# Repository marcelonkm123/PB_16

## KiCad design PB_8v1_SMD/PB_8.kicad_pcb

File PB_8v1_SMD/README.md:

# Copyright and Disclaimer
Copyright: Scott Hanson

This documentation describes Open Hardware and is licensed under the CERN Open Hardware Licence Version 2 - Strongly Reciprocal. (CERN-OHL-S)

You may redistribute and modify this documentation under the terms of the CERN OHL-S-v2 (https://ohwr.org/cern_ohl_s_v2.txt). This documentation is distributed WITHOUT ANY EXPRESS OR IMPLIED WARRANTY, INCLUDING OF MERCHANTABILITY, SATISFACTORY QUALITY AND FITNESS FOR A PARTICULAR PURPOSE. Please see the CERN OHL v2-S for applicable conditions

**Under CERN OHL-S-v2, derivative work must be publicy released as defined in subsection 3.3**

# PB 8v1

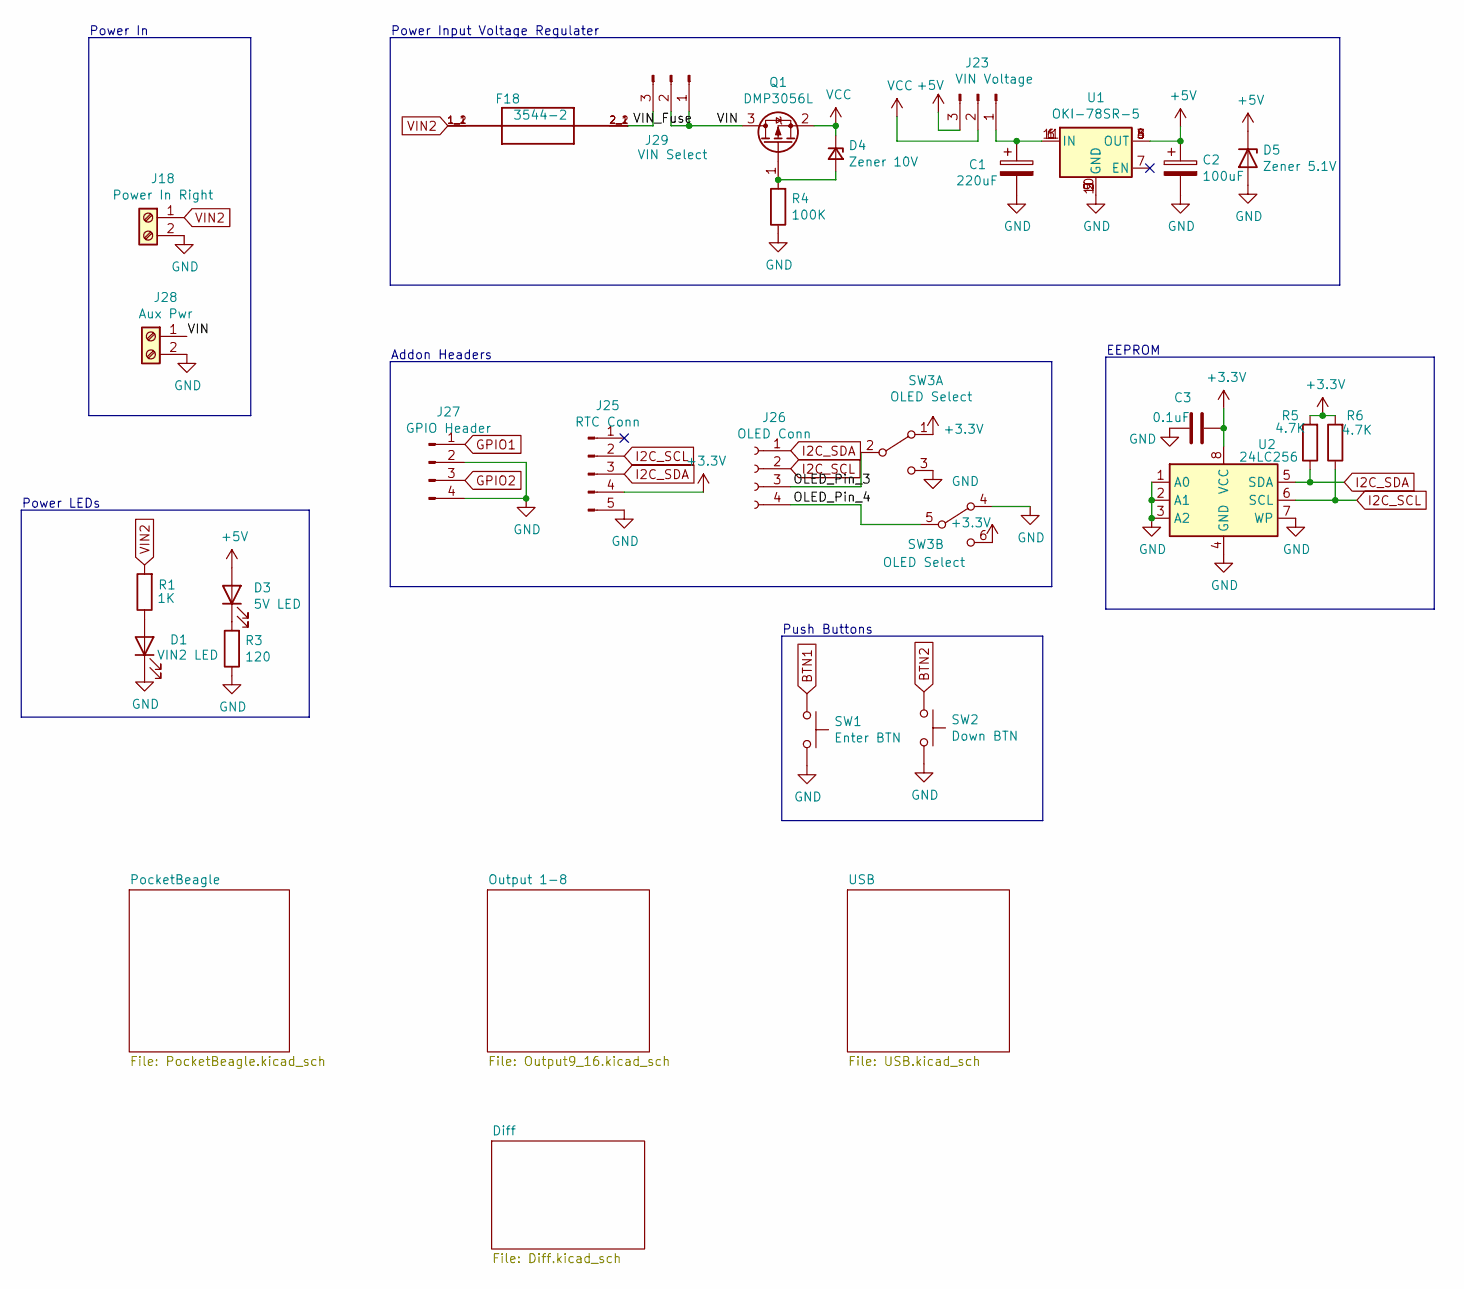
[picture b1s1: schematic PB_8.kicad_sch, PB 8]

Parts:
C1: 220uF; CP_Radial_D10.0mm_P5.00mm; MPN ECA-1HM221; Digi-Key_PN P5183-ND
C2: 100uF; CP_Elec_6.3x5.4_Nichicon; MPN UWX1C101MCL1GB; Digi-Key_PN 493-2105-1-ND
C3: 0.1uF; C_0603_1608Metric_Pad1.08x0.95mm_HandSolder; MPN CL10B104KB8NNWC; Digi-Key_PN 1276-1935-2-ND
D1: VIN2 LED; LED_0603_1608Metric_Pad1.05x0.95mm_HandSolder; MPN LTST-C190KRKT; Digi-Key_PN 160-1436-2-ND
D3: 5V LED; LED_0603_1608Metric_Pad1.05x0.95mm_HandSolder; MPN LTST-C190KRKT; Digi-Key_PN 160-1436-2-ND
D4: Zener 10V; D_SOD-123; MPN MMSZ5240B-7-F; Digi-Key_PN MMSZ5240B-FDICT-ND
D5: Zener 5.1V; D_SOD-123; MPN MMSZ5231B-7-F; Digi-Key_PN MMSZ5231B-FDICT-ND
F18: 3544-2; FUSE_3544-2; MPN 3544-2; Digi-Key_PN 36-3544-2-ND
J18: Power In Right; BARRIER_BLOCK_1ROW_2POS_P9.5MM; MPN OSTYK51102030; Digi-Key_PN ED2953-ND
J23: VIN Voltage; PinHeader_1x03_P2.54mm_Vertical; MPN 61300311121; Digi-Key_PN 732-5316-ND
J25: RTC Conn; PinHeader_1x05_P2.54mm_Vertical; MPN 61300511121; Digi-Key_PN 732-5318-ND
J26: OLED Conn; PinSocket_1x04_P2.54mm_Vertical; MPN PPTC041LFBN-RC; Digi-Key_PN S7002-ND
J27: GPIO Header; JST_XH_B4B-XH-A_1x04_P2.50mm_Vertical; MPN B4B-XH-A(LF)(SN); Digi-Key_PN 455-2249-ND
J28: Aux Pwr; PHOENIX_MKDS1_2-3.81; MPN 1727010; Digi-Key_PN 277-1947-ND
J29: VIN Select; PinHeader_1x03_P2.54mm_Vertical; MPN 61300311121; Digi-Key_PN 732-5316-ND
Q1: DMP3056L; SOT-23; MPN DMP3056L-7; Digi-Key_PN DMP3056L-7DICT-ND
R1: 1K; R_0603_1608Metric_Pad0.98x0.95mm_HandSolder; MPN RC0603FR-071KL; Digi-Key_PN 311-1.00KHRTR-ND
R3: 120; R_0603_1608Metric_Pad0.98x0.95mm_HandSolder; MPN CRGCQ0603F120R; Digi-Key_PN A129677CT-ND
R4: 100K; R_0603_1608Metric_Pad0.98x0.95mm_HandSolder; MPN RT0603BRD07100KL; Digi-Key_PN YAG1235CT-ND
R5, R6: 4.7K; R_0603_1608Metric_Pad0.98x0.95mm_HandSolder; MPN RC0603JR-074K7L; Digi-Key_PN 311-4.7KGRCT-ND
SW1: Enter BTN; SW_Push_1P1T_NO_6x6mm_H9.5mm; MPN PTS645SL50SMTR92 LFS; Digi-Key_PN CKN9088CT-ND
SW2: Down BTN; SW_Push_1P1T_NO_6x6mm_H9.5mm; MPN PTS645SL50SMTR92 LFS; Digi-Key_PN CKN9088CT-ND
SW3: OLED Select; SW_CuK_JS202011CQN_DPDT_Straight; MPN K3-2235D-F1; LCSC C189615
U1: OKI-78SR-5; Universal_5V_Horizontal; MPN OKI-78SR-5/1.5-W36-C; Digi-Key_PN 811-2196-5-ND
U2: 24LC256; SOIC-8_3.9x4.9mm_P1.27mm; MPN 24LC256T-I/SN; Digi-Key_PN 24LC256T-I/SNCT-ND

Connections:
+5V: C2.1, D3.2 (A), D5.1 (K), J23.3, U1.3 (OUT), U1.4 (OUT), U1.8 (OUT); also elsewhere on the board
/OLED_Pin_3: J26.3, SW3.2 (B)
/OLED_Pin_4: J26.4, SW3.5 (B)
/VIN: J28.1, J29.1, J29.2, Q1.3 (D)
/VIN_Fuse: F18.2_1 (2), F18.2_2 (2), J29.3
BTN1: SW1.1; also elsewhere on the board
BTN2: SW2.1; also elsewhere on the board
GPIO1: J27.1; also elsewhere on the board
GPIO2: J27.3; also elsewhere on the board
I2C_SDA: J25.3, J26.1, R5.1, U2.5 (SDA); also elsewhere on the board
unnamed: C1.1, J23.1, U1.1 (IN), U1.6 (IN), U1.11 (IN)
unnamed: D1.2 (A), R1.1
unnamed: D3.1 (K), R3.2
unnamed: D4.2 (A), Q1.1 (G), R4.2
VCC: D4.1 (K), J23.2, Q1.2 (S)
VIN2: F18.1_1 (1), F18.1_2 (1), J18.1, R1.2; also elsewhere on the board

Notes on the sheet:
Power Input Voltage Regulater
Push Buttons
Power LEDs
EEPROM
Power In
Addon Headers

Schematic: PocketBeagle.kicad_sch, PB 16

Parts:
C7: 0.1uF; C_0805_2012Metric_Pad1.15x1.40mm_HandSolder; MPN CL21F104ZBCNNNC; Digi-Key_PN 1276-1007-1-ND
U1: POCKETBEAGLE-SC-569; BEAGLE_POCKETBEAGLE-SC-569; MPN POCKETBEAGLE-SC-569; Digi-Key_PN POCKETBEAGLE-SC-569-ND

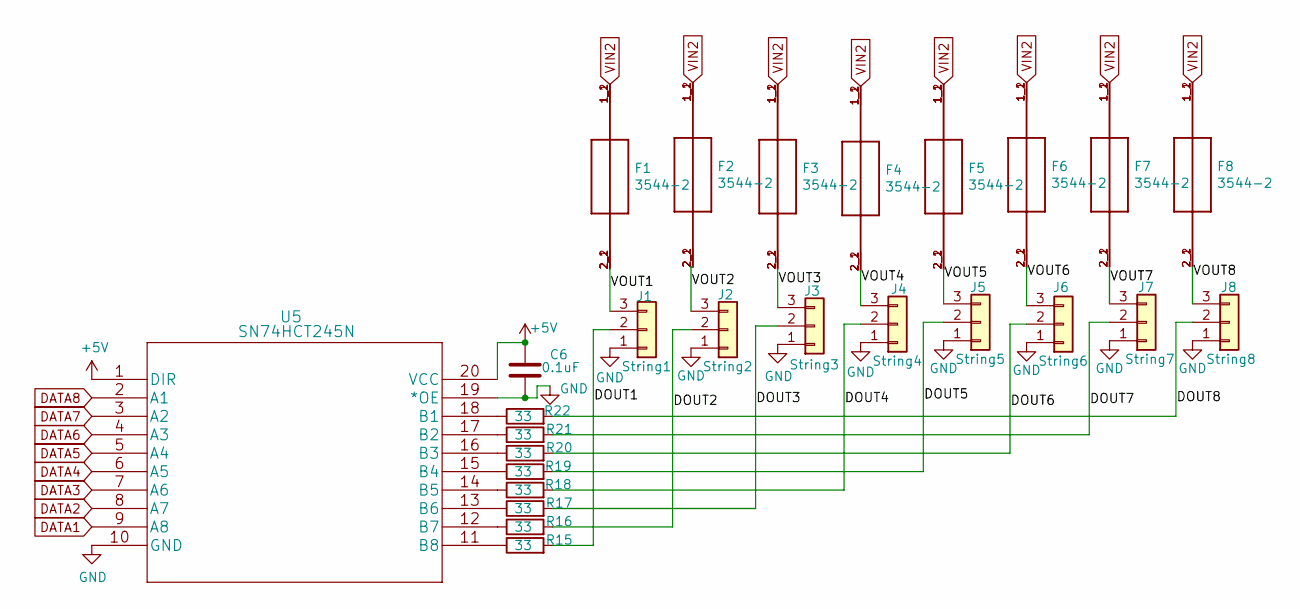
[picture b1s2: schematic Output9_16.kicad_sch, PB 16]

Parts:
C6: 0.1uF; C_0603_1608Metric_Pad1.08x0.95mm_HandSolder; MPN CL10B104KB8NNWC; Digi-Key_PN 1276-1935-2-ND
F1, F2, F3, F4, F5, F6, F7, F8: 3544-2; FUSE_3544-2; MPN 3544-2; Digi-Key_PN 36-3544-2-ND
J1: String1; PhoenixContact_MCV_1,5_3-G-3.5_1x03_P3.50mm_Vertical; MPN 1843619/OSTTJ0311530; Digi-Key_PN 277-5737-ND/ED10555-ND
J2: String2; PhoenixContact_MCV_1,5_3-G-3.5_1x03_P3.50mm_Vertical; MPN 1843619/OSTTJ0311530; Digi-Key_PN 277-5737-ND/ED10555-ND
J3: String3; PhoenixContact_MCV_1,5_3-G-3.5_1x03_P3.50mm_Vertical; MPN 1843619/OSTTJ0311530; Digi-Key_PN 277-5737-ND/ED10555-ND
J4: String4; PhoenixContact_MCV_1,5_3-G-3.5_1x03_P3.50mm_Vertical; MPN 1843619/OSTTJ0311530; Digi-Key_PN 277-5737-ND/ED10555-ND
J5: String5; PhoenixContact_MCV_1,5_3-G-3.5_1x03_P3.50mm_Vertical; MPN 1843619/OSTTJ0311530; Digi-Key_PN 277-5737-ND/ED10555-ND
J6: String6; PhoenixContact_MCV_1,5_3-G-3.5_1x03_P3.50mm_Vertical; MPN 1843619/OSTTJ0311530; Digi-Key_PN 277-5737-ND/ED10555-ND
J7: String7; PhoenixContact_MCV_1,5_3-G-3.5_1x03_P3.50mm_Vertical; MPN 1843619/OSTTJ0311530; Digi-Key_PN 277-5737-ND/ED10555-ND
J8: String8; PhoenixContact_MCV_1,5_3-G-3.5_1x03_P3.50mm_Vertical; MPN 1843619/OSTTJ0311530; Digi-Key_PN 277-5737-ND/ED10555-ND
R15, R16, R17, R18, R19, R20, R21, R22: 33; R_0603_1608Metric_Pad0.98x0.95mm_HandSolder; MPN RC0603FR-0733RL; Digi-Key_PN 311-33.0HRCT-ND
U5: SN74HCT245N; SN74HCT245NSR; MPN SN74HCT245NSR; Digi-Key_PN 296-15849-1-ND

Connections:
+5V: C6.1, U5.1 (DIR), U5.20 (VCC); also elsewhere on the board
/Output 1-8/DOUT1: J1.2, R15.2
/Output 1-8/DOUT2: J2.2, R16.2
/Output 1-8/DOUT3: J3.2, R17.2
/Output 1-8/DOUT4: J4.2, R18.2
/Output 1-8/DOUT5: J5.2, R19.2
/Output 1-8/DOUT6: J6.2, R20.2
/Output 1-8/DOUT7: J7.2, R21.2
/Output 1-8/DOUT8: J8.2, R22.2
/Output 1-8/VOUT1: F1.2_1 (2), F1.2_2 (2), J1.3
/Output 1-8/VOUT2: F2.2_1 (2), F2.2_2 (2), J2.3
/Output 1-8/VOUT3: F3.2_1 (2), F3.2_2 (2), J3.3
/Output 1-8/VOUT4: F4.2_1 (2), F4.2_2 (2), J4.3
/Output 1-8/VOUT5: F5.2_1 (2), F5.2_2 (2), J5.3
/Output 1-8/VOUT6: F6.2_1 (2), F6.2_2 (2), J6.3
/Output 1-8/VOUT7: F7.2_1 (2), F7.2_2 (2), J7.3
/Output 1-8/VOUT8: F8.2_1 (2), F8.2_2 (2), J8.3
DATA1: U5.9 (A8); also elsewhere on the board
DATA2: U5.8 (A7); also elsewhere on the board
DATA3: U5.7 (A6); also elsewhere on the board
DATA4: U5.6 (A5); also elsewhere on the board
DATA5: U5.5 (A4); also elsewhere on the board
DATA6: U5.4 (A3); also elsewhere on the board
DATA7: U5.3 (A2); also elsewhere on the board
DATA8: U5.2 (A1); also elsewhere on the board
unnamed: R15.1, U5.11 (B8)
unnamed: R16.1, U5.12 (B7)
unnamed: R17.1, U5.13 (B6)
unnamed: R18.1, U5.14 (B5)
unnamed: R19.1, U5.15 (B4)
unnamed: R20.1, U5.16 (B3)
unnamed: R21.1, U5.17 (B2)
unnamed: R22.1, U5.18 (B1)
VIN2: F1.1_1 (1), F1.1_2 (1), F2.1_1 (1), F2.1_2 (1), F3.1_1 (1), F3.1_2 (1), F4.1_1 (1), F4.1_2 (1), F5.1_1 (1), F5.1_2 (1), F6.1_1 (1), F6.1_2 (1), F7.1_1 (1), F7.1_2 (1), F8.1_1 (1), F8.1_2 (1); also elsewhere on the board

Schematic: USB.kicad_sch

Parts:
C8: 0.1uF; C_0805_2012Metric_Pad1.15x1.40mm_HandSolder; MPN CL21F104ZBCNNNC; Digi-Key_PN 1276-1007-1-ND
FB1: 150 OHM; L_0805_2012Metric_Pad1.15x1.40mm_HandSolder; MPN MU2029-151Y; Digi-Key_PN MU2029-151YCT-ND
J19: USB; USB_A_Molex_105057_Vertical; MPN 1050570001; Digi-Key_PN WM8672-ND
R6, R7: 10K; R_0805_2012Metric_Pad1.15x1.40mm_HandSolder; MPN RNCP0805FTD10K0; Digi-Key_PN RNCP0805FTD10K0CT-ND
U6: TPS2051BDBVR; SOT-753; MPN TPS2051BDBVR; Digi-Key_PN 296-21265-1-ND
U9: TPD4S009DBVR; SOT-23-6_Handsoldering; MPN TPD4S009DBVR; Digi-Key_PN 296-23749-1-ND

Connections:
/USB/V_USB_FB: FB1.1, J19.1 (VBUS)
OUT11+: R7.2; also elsewhere on the board
USB_D+: J19.3 (D+), U9.3 (D2+); also elsewhere on the board
USB_D-: J19.2 (D-), U9.4 (D2-); also elsewhere on the board
V_USB: C8.1, FB1.2, U9.5 (VCC); also elsewhere on the board

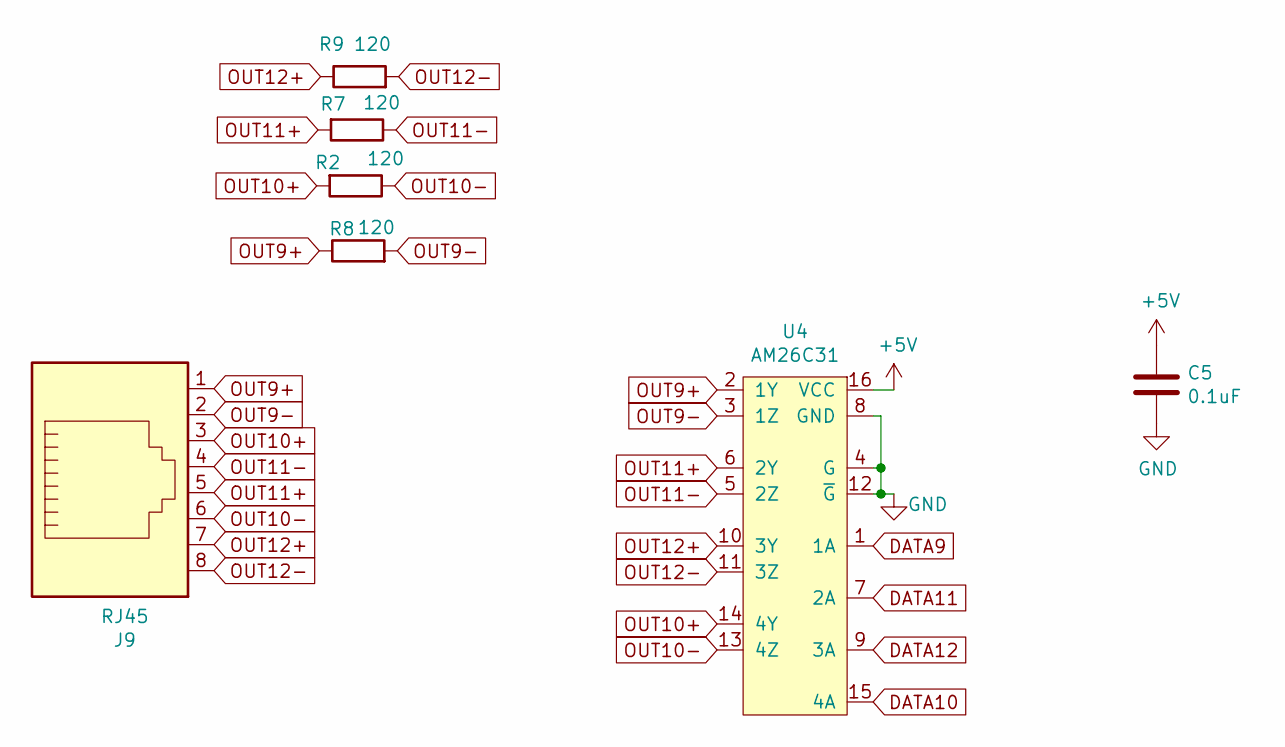
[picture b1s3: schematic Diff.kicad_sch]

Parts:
C5: 0.1uF; C_0603_1608Metric_Pad1.08x0.95mm_HandSolder; MPN CL10B104KB8NNWC; Digi-Key_PN 1276-1935-2-ND
J9: RJ45; RJ45_Amphenol_54602-x08_Horizontal; MPN X05ADIWA1DY1022; LCSC C2938579
R2, R7, R8, R9: 120; R_0603_1608Metric_Pad0.98x0.95mm_HandSolder; MPN CRGCQ0603F120R; Digi-Key_PN A129677CT-ND
U4: AM26C31; SOIC-16_3.9x9.9mm_P1.27mm; MPN AM26C31MDREP; Digikey PN 296-6785-5-ND

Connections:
+5V: C5.1, U4.16 (VCC); also elsewhere on the board
DATA9: U4.1 (1A); also elsewhere on the board
DATA10: U4.15 (4A); also elsewhere on the board
DATA11: U4.7 (2A); also elsewhere on the board
DATA12: U4.9 (3A); also elsewhere on the board
OUT9+: J9.1, R8.1, U4.2 (1Y)
OUT9-: J9.2, R8.2, U4.3 (1Z)
OUT10+: J9.3, R2.2, U4.14 (4Y)
OUT10-: J9.6, R2.1, U4.13 (4Z)
OUT11+: J9.5, R7.2, U4.6 (2Y)
OUT12+: J9.7, R9.1, U4.10 (3Y)
OUT12-: J9.8, R9.2, U4.11 (3Z)

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
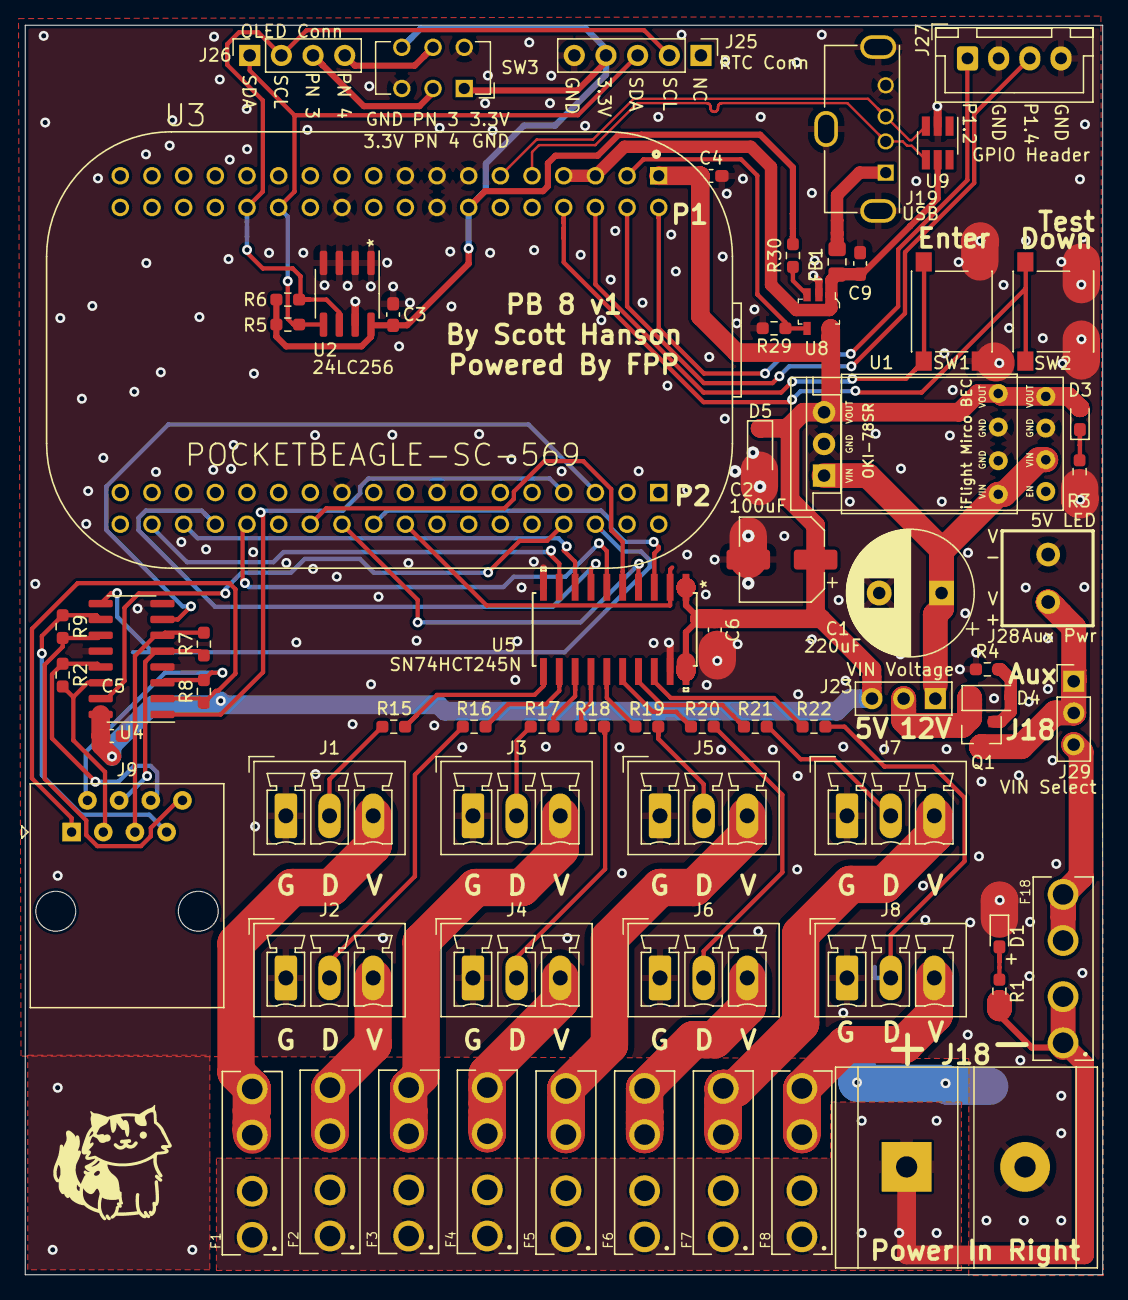
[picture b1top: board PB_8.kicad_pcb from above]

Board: 2 copper layers, 86.4 x 100.2 mm, 68 parts (0 on the bottom side), 69 nets.

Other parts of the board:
C4, C9: 0.1uF; C_0603_1608Metric_Pad1.08x0.95mm_HandSolder
R29, R30: 10K; R_0603_1608Metric_Pad0.98x0.95mm_HandSolder
U3: POCKETBEAGLE-SC-569; BEAGLE_POCKETBEAGLE-SC-569
U8: TPS2051BDBVR; SOT-753

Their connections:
+5V: C4.1, U3.P1_1 (SYS_VIN), U8.5 (IN); also elsewhere on the board
BTN1: U3.P1_6 (SPI0_CS); also elsewhere on the board
BTN2: U3.P1_8 (SPI0_CLK); also elsewhere on the board
DATA1: U3.P2_34 (PRU0_5); also elsewhere on the board
DATA2: U3.P2_32 (PRU0_2); also elsewhere on the board
DATA3: U3.P2_30 (PRU0_3); also elsewhere on the board
DATA4: U3.P2_28 (PRU0_6); also elsewhere on the board
DATA5: U3.P2_24 (GPIO_48); also elsewhere on the board
DATA6: U3.P2_22 (GPIO_46); also elsewhere on the board
DATA7: U3.P2_20 (GPIO_64); also elsewhere on the board
DATA8: U3.P2_18 (GPIO_47); also elsewhere on the board
DATA9: U3.P2_7 (UART4_TX); also elsewhere on the board
DATA10: U3.P2_8 (GPIO_60); also elsewhere on the board
DATA11: U3.P2_5 (UART4_RX); also elsewhere on the board
DATA12: U3.P2_6 (GPIO_57); also elsewhere on the board
GPIO1: U3.P1_2 (AIN6/GPIO87); also elsewhere on the board
GPIO2: U3.P1_4 (GPIO_89); also elsewhere on the board
I2C_SDA: U3.P1_26 (I2C2_SDA); also elsewhere on the board
unnamed: R30.2, U8.3 (~OC)
USB_D+: U3.P1_11 (USB1_DP); also elsewhere on the board
USB_D-: U3.P1_9 (USB1_DN); also elsewhere on the board
USB_DVBUS: R29.1, U3.P1_3 (USB1_DRVVBUS), U8.4 (~EN)
V_USB: C9.1, U3.P1_5 (USB1_VBUS), U3.P1_7 (USB1_VIN), U8.1 (OUT); also elsewhere on the board

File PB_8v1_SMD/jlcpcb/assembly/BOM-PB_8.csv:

Comment,Designator,Footprint,LCSC
150 OHM,FB1,L_0805_2012Metric_Pad1.15x1.40mm_HandSolder,C1015
Enter BTN,"SW1,SW2",SW_Push_1P1T_NO_6x6mm_H9.5mm,C127509
SN74HCT245N,U5,SN74HCT245NSR,C133641
100uF,C2,CP_Elec_6.3x5.4_Nichicon,C134723
GPIO Header,J27,JST_XH_B4B-XH-A_1x04_P2.50mm_Vertical,C144395
0.1uF,"C3,C4,C5,C6,C9",C_0603_1608Metric_Pad1.08x0.95mm_HandSolder,C14663
DMP3056L,Q1,SOT-23,C150724
Zener 5.1V,D5,D_SOD-123,C173407
Zener 10V,D4,D_SOD-123,C173431
OLED Select,SW3,SW_CuK_JS202011CQN_DPDT_Straight,C189615
String1,"J1,J2,J3,J4,J5,J6,J7,J8","PhoenixContact_MCV_1,5_3-G-3.5_1x03_P3.50mm_Vertical",C192778
1K,R1,R_0603_1608Metric_Pad0.98x0.95mm_HandSolder,C21190
OLED Conn,J26,PinSocket_1x04_P2.54mm_Vertical,C225501
120,"R2,R3,R7,R8,R9",R_0603_1608Metric_Pad0.98x0.95mm_HandSolder,C22787
VIN2 LED,"D1,D3",LED_0603_1608Metric_Pad1.05x0.95mm_HandSolder,C2286
33,"R15,R16,R17,R18,R19,R20,R21,R22",R_0603_1608Metric_Pad0.98x0.95mm_HandSolder,C23140
4.7K,"R5,R6",R_0603_1608Metric_Pad0.98x0.95mm_HandSolder,C23162
TPS2051BDBVR,U8,SOT-753,C24593
100K,R4,R_0603_1608Metric_Pad0.98x0.95mm_HandSolder,C25803
10K,"R29,R30",R_0603_1608Metric_Pad0.98x0.95mm_HandSolder,C25804
RJ45,J9,RJ45_Amphenol_54602-x08_Horizontal,C2938579
220uF,C1,CP_Radial_D10.0mm_P5.00mm,C338228
AM26C31,U4,SOIC-16_3.9x9.9mm_P1.27mm,C34923
RTC Conn,J25,PinHeader_1x05_P2.54mm_Vertical,C358687
USB,J19,USB_A_Molex_105057_Vertical,C39455
VIN Voltage,"J23,J29",PinHeader_1x03_P2.54mm_Vertical,C49257
3544-2,"F1,F18,F2,F3,F4,F5,F6,F7,F8",FUSE_3544-2,C492610
24LC256,U2,SOIC-8_3.9x4.9mm_P1.27mm,C6482
Aux Pwr,J28,PHOENIX_MKDS1_2-3.81,C69811
Power In Right,J18,BARRIER_BLOCK_1ROW_2POS_P9.5MM,C707421
TPD4S009DBVR,U9,SOT-23-6_Handsoldering,C88032
OKI-78SR-5,U1,Universal_5V_Horizontal,
POCKETBEAGLE-SC-569,U3,BEAGLE_POCKETBEAGLE-SC-569,

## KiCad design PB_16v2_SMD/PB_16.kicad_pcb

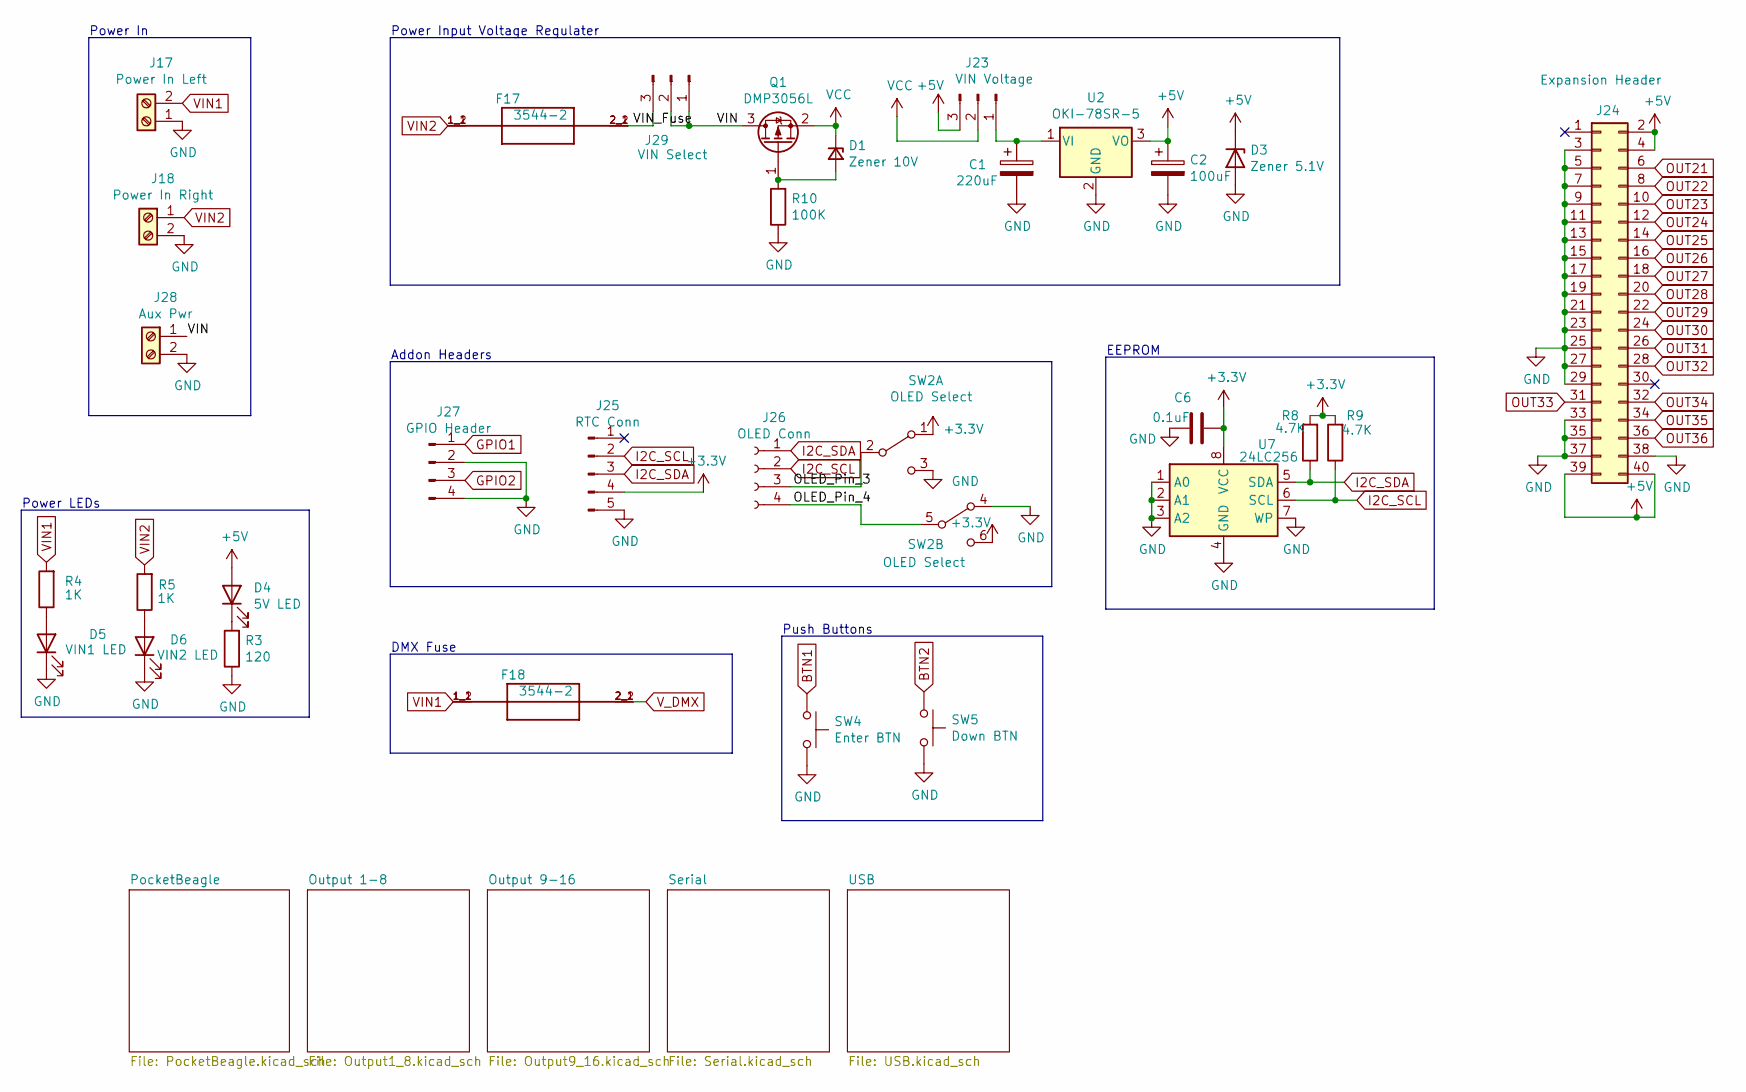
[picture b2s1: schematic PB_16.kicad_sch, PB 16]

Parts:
C1: 220uF; CP_Radial_D10.0mm_P5.00mm; MPN ECA-1HM221; Digi-Key_PN P5183-ND
C2: 100uF; CP_Elec_6.3x5.4_Nichicon; MPN UWX1C101MCL1GB; Digi-Key_PN 493-2105-1-ND
C6: 0.1uF; C_0805_2012Metric_Pad1.15x1.40mm_HandSolder; MPN CL21F104ZBCNNNC; Digi-Key_PN 1276-1007-1-ND
D1: Zener 10V; D_SOD-123; MPN MMSZ5240B-7-F; Digi-Key_PN MMSZ5240B-FDICT-ND
D3: Zener 5.1V; D_SOD-123; MPN MMSZ5231B-7-F; Digi-Key_PN MMSZ5231B-FDICT-ND
D4: 5V LED; LED_0805_2012Metric_Pad1.15x1.40mm_HandSolder; MPN LTST-C171GKT; Digi-Key_PN 160-1423-1-ND
D5: VIN1 LED; LED_0805_2012Metric_Pad1.15x1.40mm_HandSolder; MPN LTST-C171GKT; Digi-Key_PN 160-1423-1-ND
D6: VIN2 LED; LED_0805_2012Metric_Pad1.15x1.40mm_HandSolder; MPN LTST-C171GKT; Digi-Key_PN 160-1423-1-ND
F17, F18: 3544-2; FUSE_3544-2; MPN 3544-2; Digi-Key_PN 36-3544-2-ND
J17: Power In Left; BARRIER_BLOCK_1ROW_2POS_P9.5MM; MPN OSTYK51102030; Digi-Key_PN ED2953-ND
J18: Power In Right; BARRIER_BLOCK_1ROW_2POS_P9.5MM; MPN OSTYK51102030; Digi-Key_PN ED2953-ND
J23: VIN Voltage; PinHeader_1x03_P2.54mm_Vertical; MPN 61300311121; Digi-Key_PN 732-5316-ND
J24: Expansion Header; IDC-Header_2x20_P2.54mm_Vertical; MPN SBH11-PBPC-D20-ST-BK; Digi-Key_PN S9175-ND
J25: RTC Conn; PinHeader_1x05_P2.54mm_Vertical; MPN 61300511121; Digi-Key_PN 732-5318-ND
J26: OLED Conn; PinSocket_1x04_P2.54mm_Vertical; MPN PPTC041LFBN-RC; Digi-Key_PN S7002-ND
J27: GPIO Header; JST_XH_B4B-XH-A_1x04_P2.50mm_Vertical; MPN B4B-XH-A(LF)(SN); Digi-Key_PN 455-2249-ND
J28: Aux Pwr; PHOENIX_MKDS1_2-3.81; MPN 1727010; Digi-Key_PN 277-1947-ND
J29: VIN Select; PinHeader_1x03_P2.54mm_Vertical; MPN 61300311121; Digi-Key_PN 732-5316-ND
Q1: DMP3056L; SOT-23; MPN DMP3056L-7; Digi-Key_PN DMP3056L-7DICT-ND
R3: 120; R_0805_2012Metric_Pad1.15x1.40mm_HandSolder; MPN RC0805JR-07120RL; Digi-Key_PN 311-120ARCT-ND
R4, R5: 1K; R_0805_2012Metric_Pad1.15x1.40mm_HandSolder; MPN RNCP0805FTD1K00; Digi-Key_PN RNCP0805FTD1K00CT-ND
R8, R9: 4.7K; R_0805_2012Metric_Pad1.15x1.40mm_HandSolder; MPN RC0805JR-074K7L; Digi-Key_PN 311-4.7KARCT-ND
R10: 100K; R_0805_2012Metric_Pad1.15x1.40mm_HandSolder; MPN RC0805FR-07100KL; Digi-Key_PN 311-100KCRCT-ND
SW2: OLED Select; SW_CuK_JS202011CQN_DPDT_Straight; MPN JS202011JCQN; Digi-Key_PN CKN10723CT-ND
SW4: Enter BTN; SW_Push_1P1T_NO_6x6mm_H9.5mm; MPN PTS645SL50SMTR92 LFS; Digi-Key_PN CKN9088CT-ND
SW5: Down BTN; SW_Push_1P1T_NO_6x6mm_H9.5mm; MPN PTS645SL50SMTR92 LFS; Digi-Key_PN CKN9088CT-ND
U2: OKI-78SR-5; Converter_DCDC_muRata_OKI-78SR_Horizontal; MPN OKI-78SR-5/1.5-W36-C; Digi-Key_PN 811-2196-5-ND
U7: 24LC256; SOIC-8_3.9x4.9mm_P1.27mm; MPN 24LC256T-I/SN; Digi-Key_PN 24LC256T-I/SNCT-ND

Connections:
+3V3: C6.1, J25.4, R8.2, R9.2, SW2.1 (A), SW2.6 (C), U7.8 (VCC); also elsewhere on the board
+5V: C2.1, D3.1 (K), D4.2 (A), J23.3, J24.2, J24.4, J24.39, J24.40, U2.3 (VO); also elsewhere on the board
/OLED_Pin_3: J26.3, SW2.2 (B)
/OLED_Pin_4: J26.4, SW2.5 (B)
/VIN: J28.1, J29.1, J29.2, Q1.3 (D)
/VIN_Fuse: F17.2_1 (2), F17.2_2 (2), J29.3
BTN1: SW4.1; also elsewhere on the board
BTN2: SW5.1; also elsewhere on the board
GND: C1.2, C2.2, C6.2, D3.2 (A), D5.1 (K), D6.1 (K), J17.1, J18.2, J24.3, J24.5, J24.7, J24.9, J24.11, J24.13, J24.15, J24.17, J24.19, J24.21, J24.23, J24.25, J24.27, J24.29, J24.33, J24.35, J24.37, J24.38, J25.5, J27.2, J27.4, J28.2, R3.1, R10.1, SW2.3 (C), SW2.4 (A), SW4.2, SW5.2, U2.2 (GND), U7.1 (A0), U7.2 (A1), U7.3 (A2), U7.4 (GND), U7.7 (WP); also elsewhere on the board
GPIO1: J27.1; also elsewhere on the board
GPIO2: J27.3; also elsewhere on the board
I2C_SCL: J25.2, J26.2, R9.1, U7.6 (SCL); also elsewhere on the board
I2C_SDA: J25.3, J26.1, R8.1, U7.5 (SDA); also elsewhere on the board
unnamed: C1.1, J23.1, U2.1 (VI)
unnamed: D1.2 (A), Q1.1 (G), R10.2
unnamed: D4.1 (K), R3.2
unnamed: D5.2 (A), R4.1
unnamed: D6.2 (A), R5.1
OUT21: J24.6; also elsewhere on the board
OUT22: J24.8; also elsewhere on the board
OUT23: J24.10; also elsewhere on the board
OUT24: J24.12; also elsewhere on the board
OUT25: J24.14; also elsewhere on the board
OUT26: J24.16; also elsewhere on the board
OUT27: J24.18; also elsewhere on the board
OUT28: J24.20; also elsewhere on the board
OUT29: J24.22; also elsewhere on the board
OUT30: J24.24; also elsewhere on the board
OUT31: J24.26; also elsewhere on the board
OUT32: J24.28; also elsewhere on the board
OUT33: J24.31; also elsewhere on the board
OUT34: J24.32; also elsewhere on the board
OUT35: J24.34; also elsewhere on the board
OUT36: J24.36; also elsewhere on the board
VCC: D1.1 (K), J23.2, Q1.2 (S)
VIN1: F18.1_1 (1), F18.1_2 (1), J17.2, R4.2; also elsewhere on the board
VIN2: F17.1_1 (1), F17.1_2 (1), J18.1, R5.2; also elsewhere on the board
V_DMX: F18.2_1 (2), F18.2_2 (2); also elsewhere on the board

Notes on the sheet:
DMX Fuse
EEPROM
Addon Headers
Push Buttons
Power In
Power Input Voltage Regulater
Power LEDs

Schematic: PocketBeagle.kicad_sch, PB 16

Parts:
C7: 0.1uF; C_0805_2012Metric_Pad1.15x1.40mm_HandSolder; MPN CL21F104ZBCNNNC; Digi-Key_PN 1276-1007-1-ND
U1: POCKETBEAGLE-SC-569; BEAGLE_POCKETBEAGLE-SC-569; MPN POCKETBEAGLE-SC-569; Digi-Key_PN POCKETBEAGLE-SC-569-ND

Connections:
+3V3: U1.P1_14; also elsewhere on the board
+5V: C7.1, U1.P1_1; also elsewhere on the board
BTN1: U1.P1_6; also elsewhere on the board
BTN2: U1.P1_8; also elsewhere on the board
DATA1: U1.P2_34; also elsewhere on the board
DATA2: U1.P2_32; also elsewhere on the board
DATA3: U1.P2_30; also elsewhere on the board
DATA4: U1.P2_28; also elsewhere on the board
DATA5: U1.P2_24; also elsewhere on the board
DATA6: U1.P2_22; also elsewhere on the board
DATA7: U1.P2_20; also elsewhere on the board
DATA8: U1.P2_18; also elsewhere on the board
DATA9: U1.P2_7; also elsewhere on the board
DATA10: U1.P2_8; also elsewhere on the board
DATA11: U1.P2_5; also elsewhere on the board
DATA12: U1.P2_6; also elsewhere on the board
DATA13: U1.P2_4; also elsewhere on the board
DATA14: U1.P2_3; also elsewhere on the board
DATA15: U1.P2_2; also elsewhere on the board
DATA16: U1.P2_1; also elsewhere on the board
GND: C7.2, U1.P1_13, U1.P1_15, U1.P1_16, U1.P1_17, U1.P1_22, U1.P2_15, U1.P2_21; also elsewhere on the board
GPIO1: U1.P1_2; also elsewhere on the board
GPIO2: U1.P1_4; also elsewhere on the board
I2C_SCL: U1.P1_28; also elsewhere on the board
I2C_SDA: U1.P1_26; also elsewhere on the board
OUT17: U1.P2_33
OUT18: U1.P2_35
OUT19: U1.P2_29
OUT20: U1.P2_31
OUT21: U1.P1_29; also elsewhere on the board
OUT22: U1.P1_31; also elsewhere on the board
OUT23: U1.P1_33; also elsewhere on the board
OUT24: U1.P1_35; also elsewhere on the board
OUT25: U1.P1_34; also elsewhere on the board
OUT26: U1.P1_36; also elsewhere on the board
OUT27: U1.P1_32; also elsewhere on the board
OUT28: U1.P1_30; also elsewhere on the board
OUT29: U1.P1_20; also elsewhere on the board
OUT30: U1.P1_12; also elsewhere on the board
OUT31: U1.P2_10; also elsewhere on the board
OUT32: U1.P2_11; also elsewhere on the board
OUT33: U1.P2_17; also elsewhere on the board
OUT34: U1.P2_19; also elsewhere on the board
OUT35: U1.P2_25; also elsewhere on the board
OUT36: U1.P2_27; also elsewhere on the board
TXD1: U1.P2_9; also elsewhere on the board
TXD2: U1.P1_10; also elsewhere on the board
USB_D+: U1.P1_11; also elsewhere on the board
USB_D-: U1.P1_9; also elsewhere on the board
USB_DVBUS: U1.P1_3; also elsewhere on the board
V_USB: U1.P1_5, U1.P1_7; also elsewhere on the board

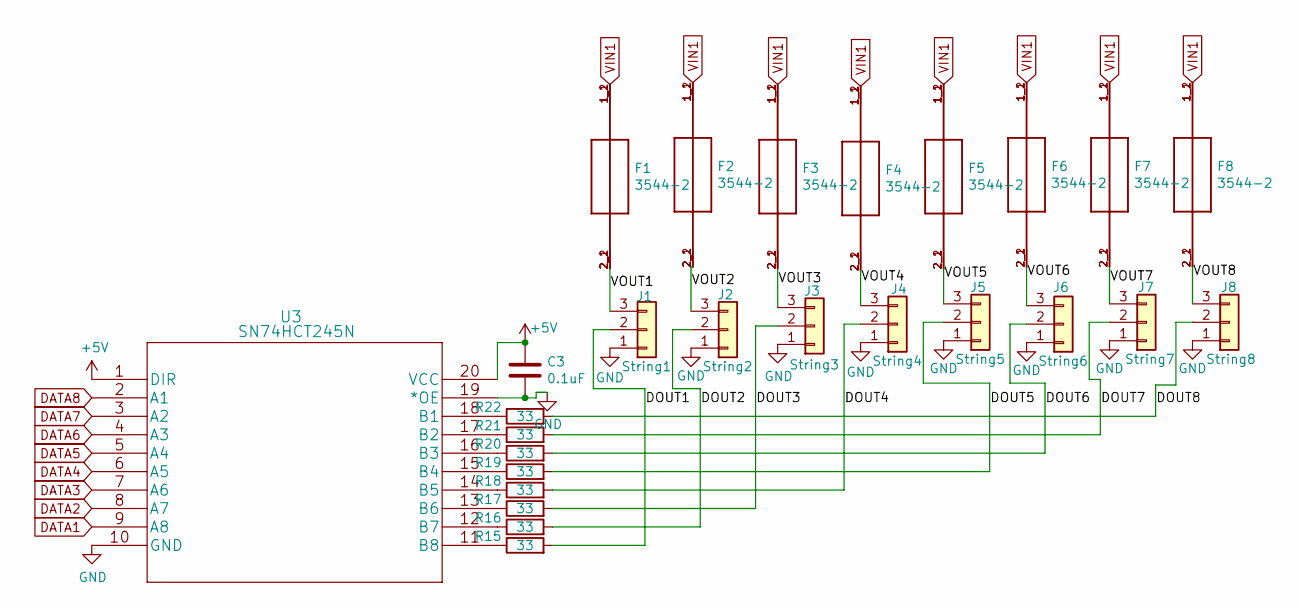
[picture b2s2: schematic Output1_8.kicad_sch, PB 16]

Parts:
C3: 0.1uF; C_0805_2012Metric_Pad1.15x1.40mm_HandSolder; MPN CL21F104ZBCNNNC; Digi-Key_PN 1276-1007-1-ND
F1, F2, F3, F4, F5, F6, F7, F8: 3544-2; FUSE_3544-2; MPN 3544-2; Digi-Key_PN 36-3544-2-ND
J1: String1; PhoenixContact_MCV_1,5_3-G-3.5_1x03_P3.50mm_Vertical; MPN 1843619/OSTTJ0311530; Digi-Key_PN 277-5737-ND/ED10555-ND
J2: String2; PhoenixContact_MCV_1,5_3-G-3.5_1x03_P3.50mm_Vertical; MPN 1843619/OSTTJ0311530; Digi-Key_PN 277-5737-ND/ED10555-ND
J3: String3; PhoenixContact_MCV_1,5_3-G-3.5_1x03_P3.50mm_Vertical; MPN 1843619/OSTTJ0311530; Digi-Key_PN 277-5737-ND/ED10555-ND
J4: String4; PhoenixContact_MCV_1,5_3-G-3.5_1x03_P3.50mm_Vertical; MPN 1843619/OSTTJ0311530; Digi-Key_PN 277-5737-ND/ED10555-ND
J5: String5; PhoenixContact_MCV_1,5_3-G-3.5_1x03_P3.50mm_Vertical; MPN 1843619/OSTTJ0311530; Digi-Key_PN 277-5737-ND/ED10555-ND
J6: String6; PhoenixContact_MCV_1,5_3-G-3.5_1x03_P3.50mm_Vertical; MPN 1843619/OSTTJ0311530; Digi-Key_PN 277-5737-ND/ED10555-ND
J7: String7; PhoenixContact_MCV_1,5_3-G-3.5_1x03_P3.50mm_Vertical; MPN 1843619/OSTTJ0311530; Digi-Key_PN 277-5737-ND/ED10555-ND
J8: String8; PhoenixContact_MCV_1,5_3-G-3.5_1x03_P3.50mm_Vertical; MPN 1843619/OSTTJ0311530; Digi-Key_PN 277-5737-ND/ED10555-ND
R15, R16, R17, R18, R19, R20, R21, R22: 33; R_0603_1608Metric_Pad0.98x0.95mm_HandSolder; MPN CN34J330CT; LCSC C23140
U3: SN74HCT245N; SN74HCT245NSR; MPN SN74HCT245NSR; Digi-Key_PN 296-15849-1-ND

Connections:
+5V: C3.1, U3.1 (DIR), U3.20 (VCC); also elsewhere on the board
/Output 1-8/DOUT1: J1.2, R15.2
/Output 1-8/DOUT2: J2.2, R16.2
/Output 1-8/DOUT3: J3.2, R17.2
/Output 1-8/DOUT4: J4.2, R18.2
/Output 1-8/DOUT5: J5.2, R19.2
/Output 1-8/DOUT6: J6.2, R20.2
/Output 1-8/DOUT7: J7.2, R21.2
/Output 1-8/DOUT8: J8.2, R22.2
/Output 1-8/VOUT1: F1.2_1 (2), F1.2_2 (2), J1.3
/Output 1-8/VOUT2: F2.2_1 (2), F2.2_2 (2), J2.3
/Output 1-8/VOUT3: F3.2_1 (2), F3.2_2 (2), J3.3
/Output 1-8/VOUT4: F4.2_1 (2), F4.2_2 (2), J4.3
/Output 1-8/VOUT5: F5.2_1 (2), F5.2_2 (2), J5.3
/Output 1-8/VOUT6: F6.2_1 (2), F6.2_2 (2), J6.3
/Output 1-8/VOUT7: F7.2_1 (2), F7.2_2 (2), J7.3
/Output 1-8/VOUT8: F8.2_1 (2), F8.2_2 (2), J8.3
DATA1: U3.9 (A8); also elsewhere on the board
DATA2: U3.8 (A7); also elsewhere on the board
DATA3: U3.7 (A6); also elsewhere on the board
DATA4: U3.6 (A5); also elsewhere on the board
DATA5: U3.5 (A4); also elsewhere on the board
DATA6: U3.4 (A3); also elsewhere on the board
DATA7: U3.3 (A2); also elsewhere on the board
DATA8: U3.2 (A1); also elsewhere on the board
GND: C3.2, J1.1, J2.1, J3.1, J4.1, J5.1, J6.1, J7.1, J8.1, U3.10 (GND), U3.19 (*OE); also elsewhere on the board
unnamed: R15.1, U3.11 (B8)
unnamed: R16.1, U3.12 (B7)
unnamed: R17.1, U3.13 (B6)
unnamed: R18.1, U3.14 (B5)
unnamed: R19.1, U3.15 (B4)
unnamed: R20.1, U3.16 (B3)
unnamed: R21.1, U3.17 (B2)
unnamed: R22.1, U3.18 (B1)
VIN1: F1.1_1 (1), F1.1_2 (1), F2.1_1 (1), F2.1_2 (1), F3.1_1 (1), F3.1_2 (1), F4.1_1 (1), F4.1_2 (1), F5.1_1 (1), F5.1_2 (1), F6.1_1 (1), F6.1_2 (1), F7.1_1 (1), F7.1_2 (1), F8.1_1 (1), F8.1_2 (1); also elsewhere on the board

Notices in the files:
parts and their libraries:
Copyright 2016 Accelerated Designs. All rights reserved.
